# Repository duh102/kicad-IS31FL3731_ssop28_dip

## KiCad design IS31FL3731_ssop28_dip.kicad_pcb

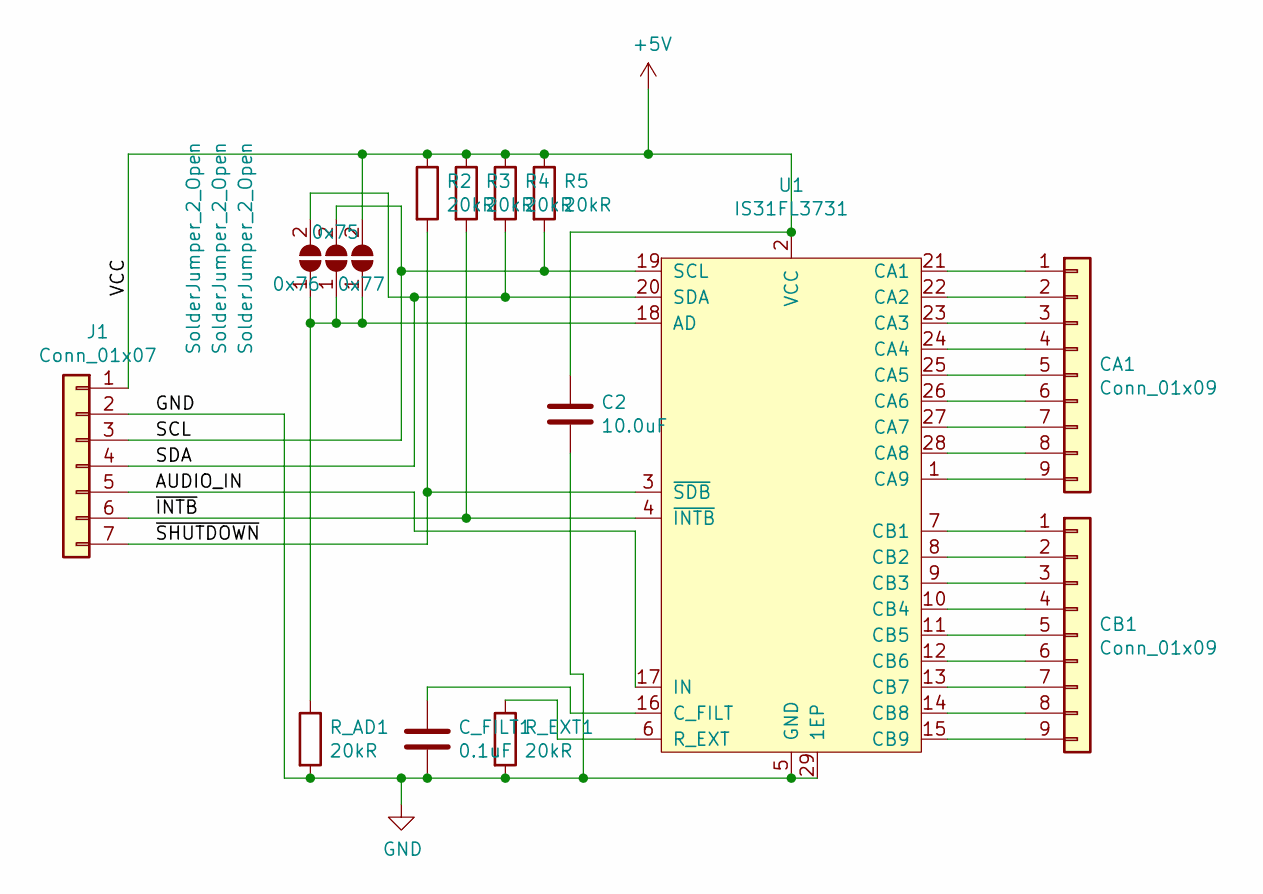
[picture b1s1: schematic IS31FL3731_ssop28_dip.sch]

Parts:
0x75, 0x76, 0x77: SolderJumper_2_Open; SolderJumper-2_P1.3mm_Open_TrianglePad1.0x1.5mm
C2: 10.0uF; C_0805_2012Metric
CA1: Conn_01x09; PinHeader_1x09_P2.54mm_Vertical
CB1: Conn_01x09; PinHeader_1x09_P2.54mm_Vertical
C_FILT1: 0.1uF; C_0805_2012Metric
J1: Conn_01x07; PinHeader_1x07_P2.54mm_Vertical
R2, R3, R4, R5: 20kR; R_0805_2012Metric
R_AD1: 20kR; R_0805_2012Metric
R_EXT1: 20kR; R_0805_2012Metric
U1: IS31FL3731; SSOP-28_5.3x10.2mm_P0.65mm

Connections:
+5V: 0x77.2 (B), C2.1, J1.1, R2.1, R3.1, R4.1, R5.1, U1.2 (VCC)
/AUDIO_IN: J1.5, U1.17 (IN)
/SCL: 0x75.2 (B), J1.3, R5.2, U1.19 (SCL)
/SDA: 0x76.2 (B), J1.4, R4.2, U1.20 (SDA)
/~INTB: J1.6, R3.2, U1.4 (~INTB)
/~SHUTDOWN: J1.7, R2.2, U1.3 (~SDB)
GND: C2.2, C_FILT1.2, J1.2, R_AD1.2, R_EXT1.2, U1.5 (GND), U1.29 (1EP)
unnamed: 0x75.1 (A), 0x76.1 (A), 0x77.1 (A), R_AD1.1, U1.18 (AD)
unnamed: CA1.1, U1.21 (CA1)
unnamed: CA1.2, U1.22 (CA2)
unnamed: CA1.3, U1.23 (CA3)
unnamed: CA1.4, U1.24 (CA4)
unnamed: CA1.5, U1.25 (CA5)
unnamed: CA1.6, U1.26 (CA6)
unnamed: CA1.7, U1.27 (CA7)
unnamed: CA1.8, U1.28 (CA8)
unnamed: CA1.9, U1.1 (CA9)
unnamed: CB1.1, U1.7 (CB1)
unnamed: CB1.2, U1.8 (CB2)
unnamed: CB1.3, U1.9 (CB3)
unnamed: CB1.4, U1.10 (CB4)
unnamed: CB1.5, U1.11 (CB5)
unnamed: CB1.6, U1.12 (CB6)
unnamed: CB1.7, U1.13 (CB7)
unnamed: CB1.8, U1.14 (CB8)
unnamed: CB1.9, U1.15 (CB9)
unnamed: C_FILT1.1, U1.16 (C_FILT)
unnamed: R_EXT1.1, U1.6 (R_EXT)

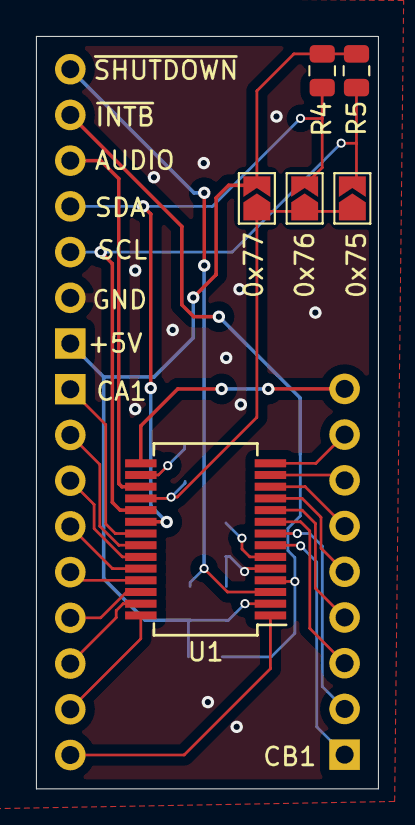
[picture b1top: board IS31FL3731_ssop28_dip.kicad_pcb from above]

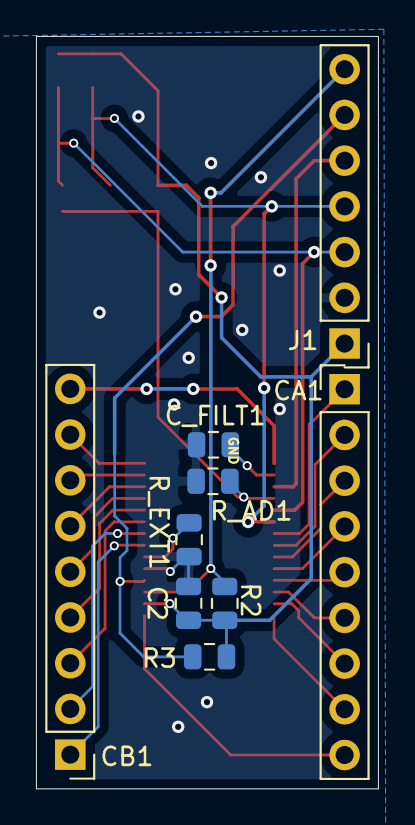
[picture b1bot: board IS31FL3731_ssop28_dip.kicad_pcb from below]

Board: 2 copper layers, 19.0 x 41.8 mm, 15 parts (9 on the bottom side), 28 nets.

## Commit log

2019-11-24 Route everything for ssop28
2019-11-24 Fix labels
